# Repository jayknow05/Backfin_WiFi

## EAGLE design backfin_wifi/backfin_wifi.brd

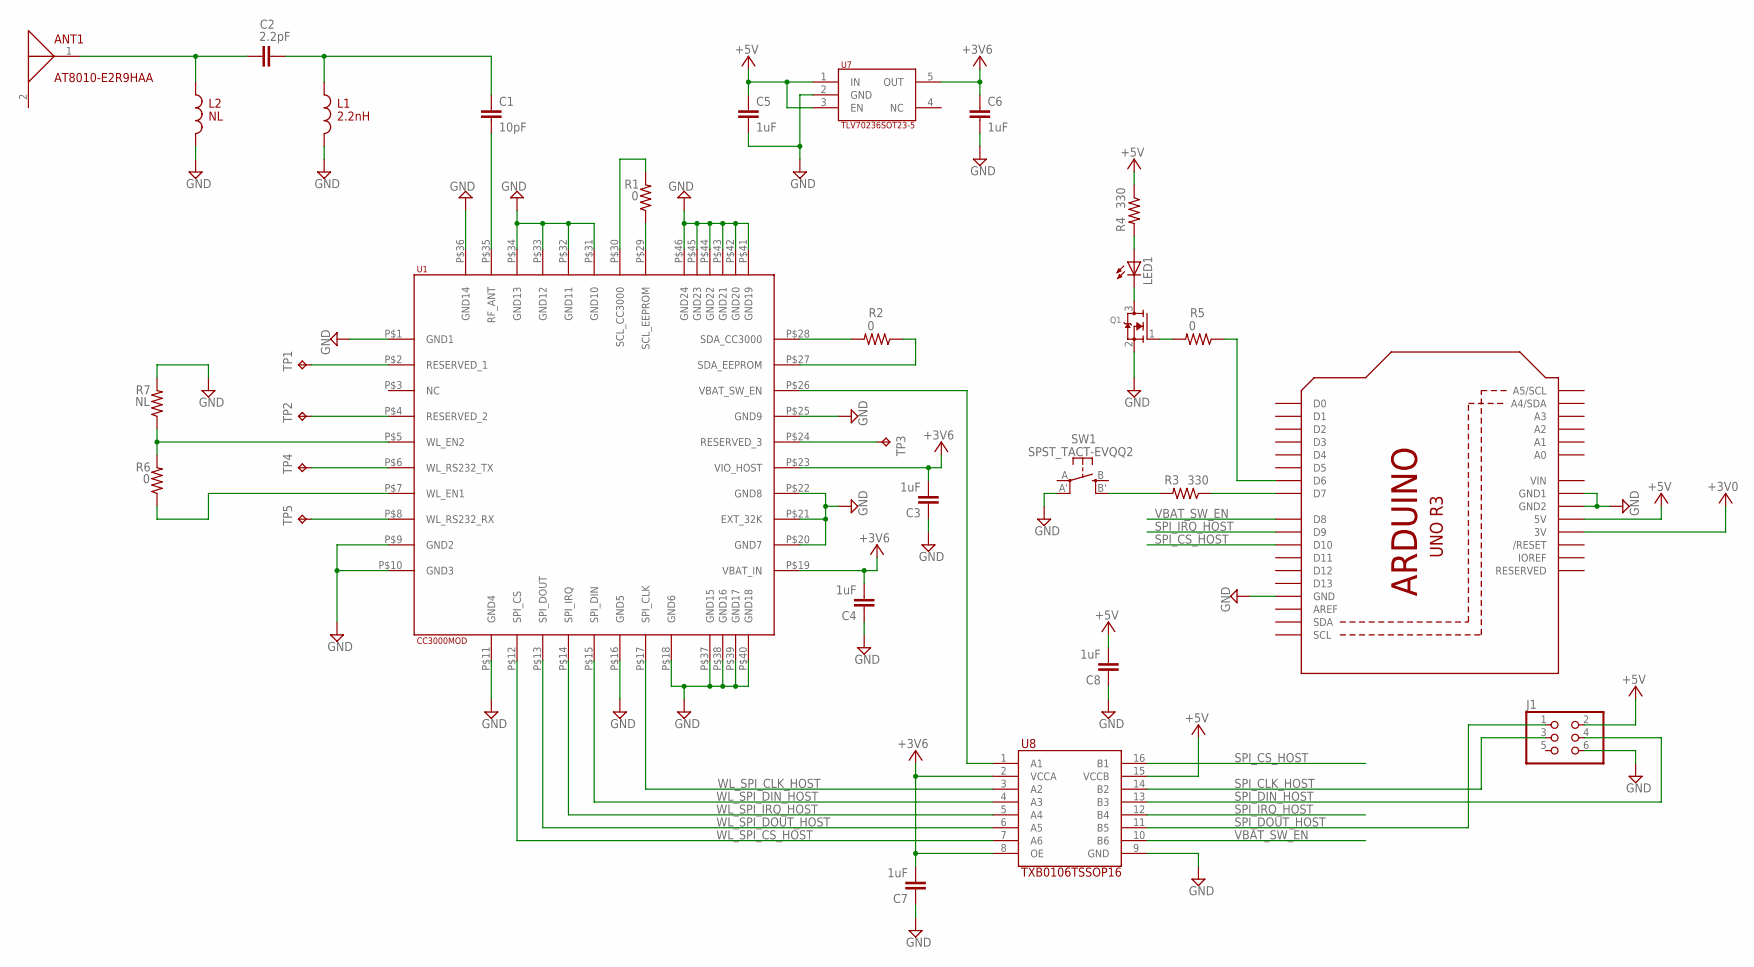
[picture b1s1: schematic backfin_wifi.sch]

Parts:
ANT1: AT8010-E2R9HAA
C1: 10pF; C0402K
C2: 2.2pF; C0402K
C3, C4, C5, C6, C7, C8: 1uF; C0402K
J1: PINHD-2X3; 2X03
L1: 2.2nH; 0402
L2: NL; 0402
LED1: LEDCHIPLED_1206; CHIPLED_1206
Q1: MOSFET-NREFLOW; SOT23
R1, R2, R5, R6: 0; R1005
R3, R4: 330; R1005
R7: NL; R1005
SW1: SPST_TACT-EVQQ2; EVQ-Q2
TP1, TP2, TP3, TP4, TP5: TPB1,27; B1,27
U1: CC3000MOD
U2: ARDUINOR3-DIMENSION; ARDUINOR3
U7: TLV70236SOT23-5; SOT23-DBV
U8: TXB0106TSSOP16; TSSOP16

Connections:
+3V3: U2.3V
+5V: C5.1, C8.2, J1.2, R4.1, U2.5V, U7.1 (IN), U7.3 (EN), U8.15 (VCCB)
GND: C3.1, C4.1, C5.2, C6.2, C7.1, C8.1, J1.6, L1.2, L2.2, Q1.2 (S), R7.2, SW1.A' (P1), U1.P$1 (GND1), U1.P$9 (GND2), U1.P$10 (GND3), U1.P$11 (GND4), U1.P$16 (GND5), U1.P$18 (GND6), U1.P$20 (GND7), U1.P$21 (EXT_32K), U1.P$22 (GND8), U1.P$25 (GND9), U1.P$31 (GND10), U1.P$32 (GND11), U1.P$33 (GND12), U1.P$34 (GND13), U1.P$36 (GND14), U1.P$37 (GND15), U1.P$38 (GND16), U1.P$39 (GND17), U1.P$40 (GND18), U1.P$41 (GND19), U1.P$42 (GND20), U1.P$43 (GND21), U1.P$44 (GND22), U1.P$45 (GND23), U1.P$46 (GND24), U2.GND, U2.GND1, U2.GND2, U7.2 (GND), U8.9 (GND)
unnamed: R6.1, U1.P$7 (WL_EN1)
unnamed: R6.2, R7.1, U1.P$5 (WL_EN2)
unnamed: TP1.TP, U1.P$2 (RESERVED_1)
unnamed: TP2.TP, U1.P$4 (RESERVED_2)
unnamed: TP4.TP, U1.P$6 (WL_RS232_TX)
unnamed: TP5.TP, U1.P$8 (WL_RS232_RX)
unnamed: TP3.TP, U1.P$24 (RESERVED_3)
unnamed: R2.2, U1.P$28 (SDA_CC3000)
unnamed: R2.1, U1.P$27 (SDA_EEPROM)
unnamed: R1.1, U1.P$29 (SCL_EEPROM)
unnamed: R1.2, U1.P$30 (SCL_CC3000)
unnamed: C1.2, U1.P$35 (RF_ANT)
unnamed: C1.1, C2.2, L1.1
unnamed: Q1.1 (G), R5.2
unnamed: ANT1.1 (FEED), C2.1, L2.1
unnamed: U1.P$26 (VBAT_SW_EN), U8.1 (A1)
unnamed: R3.1, U2.D7
unnamed: R3.2, SW1.B' (S1)
unnamed: R5.1, U2.D6
unnamed: LED1.C, Q1.3 (D)
unnamed: LED1.A, R4.2
SPI_CLK_HOST: J1.3, U8.14 (B2)
SPI_CS_HOST: U2.D10, U8.16 (B1)
SPI_DIN_HOST: J1.4, U8.13 (B3)
SPI_DOUT_HOST: J1.1, U8.11 (B5)
SPI_IRQ_HOST: U2.D9, U8.12 (B4)
VBAT_SW_EN: U2.D8, U8.10 (B6)
VCC: C3.2, C4.2, C6.1, C7.2, U1.P$19 (VBAT_IN), U1.P$23 (VIO_HOST), U7.5 (OUT), U8.2 (VCCA), U8.8 (OE)
VIN: U2.VIN
WL_SPI_CLK_HOST: U1.P$17 (SPI_CLK), U8.3 (A2)
WL_SPI_CS_HOST: U1.P$12 (SPI_CS), U8.7 (A6)
WL_SPI_DIN_HOST: U1.P$15 (SPI_DIN), U8.4 (A3)
WL_SPI_DOUT_HOST: U1.P$13 (SPI_DOUT), U8.6 (A5)
WL_SPI_IRQ_HOST: U1.P$14 (SPI_IRQ), U8.5 (A4)

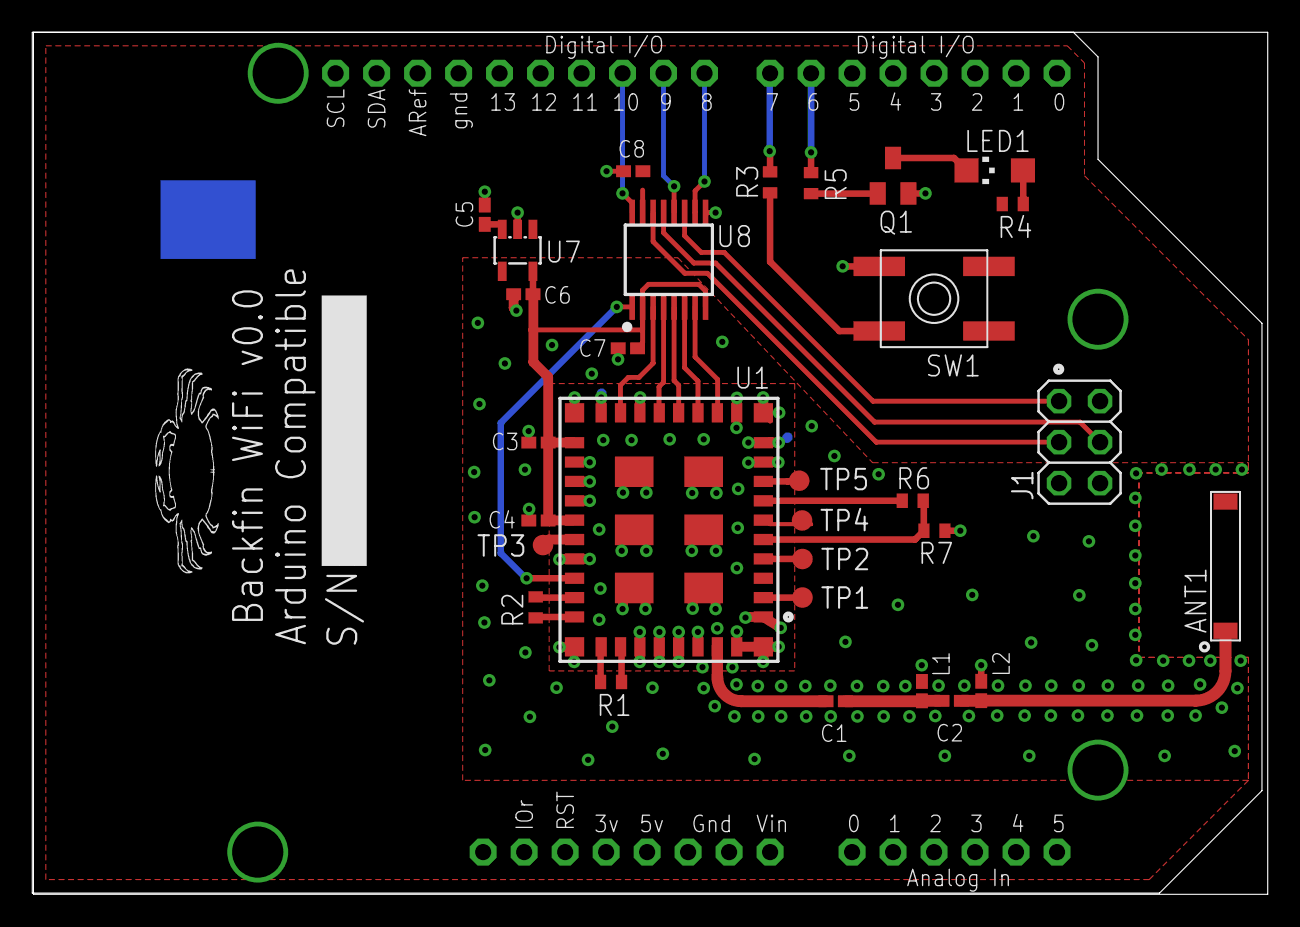
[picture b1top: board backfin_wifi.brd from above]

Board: 2 copper layers, 76.6 x 53.4 mm, 31 parts (0 on the bottom side), 35 nets.

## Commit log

2013-01-25 Created repository...
2013-01-25 Added some files...
2013-01-25 Added external_lbrs
2013-01-25 First cut V0.0
2013-01-26 Cost estimate, library updates...
2013-01-26 Added push button and LED
2013-02-05 more work...
2013-02-05 Initial placement complete...
2013-02-06 Only transmission line remains...
    Contacted 4PCB to see what their $33 standard stackup is.
2013-02-07 Waveguide complete....
2013-02-08 Ready for ordering...
2013-02-08 Ready for ordering (14mil vias)
2013-02-08 Added logo, and fixed edge keepout...
2013-02-08 Created Gerbers...
2013-02-13 Worked on library code.
2013-02-14 Interrupt code
    Added interrupt code, needed to move the IRQ to pin 3 since it and pin 2
    are the only available interrupt pins. This will have to be a mod to the
    board.
2013-02-15 Fixed interrupt levels, added some debugging...
    Doesn't seem to be getting through all 60 values in the buffer...
2013-02-17 late night code sesh results.
2013-05-16 Update after a few month's hiatus...
